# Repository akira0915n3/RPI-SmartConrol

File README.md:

# RPI-SmartConrol
RaspberryPi Zero 用赤外線読み取り、赤外線信号の発信シールドです。<br>
SMD部品を使用しているため、制作難易度は高めです。<br>
部品は秋月電子ですべて揃うはずです。

- Pin配置

|PIN No.|Sources|
|-------|-------|
|Pin 1  |3.3V   |
|Pin 2  |5V     |
|Pin 6  |GND    |
|GPIO 17|LED    |
|GPIO 18|LEDRead|
|Pin 17 |3.3V   |
|Pin 30 |GND    |
|GPIO 12|CN1    |

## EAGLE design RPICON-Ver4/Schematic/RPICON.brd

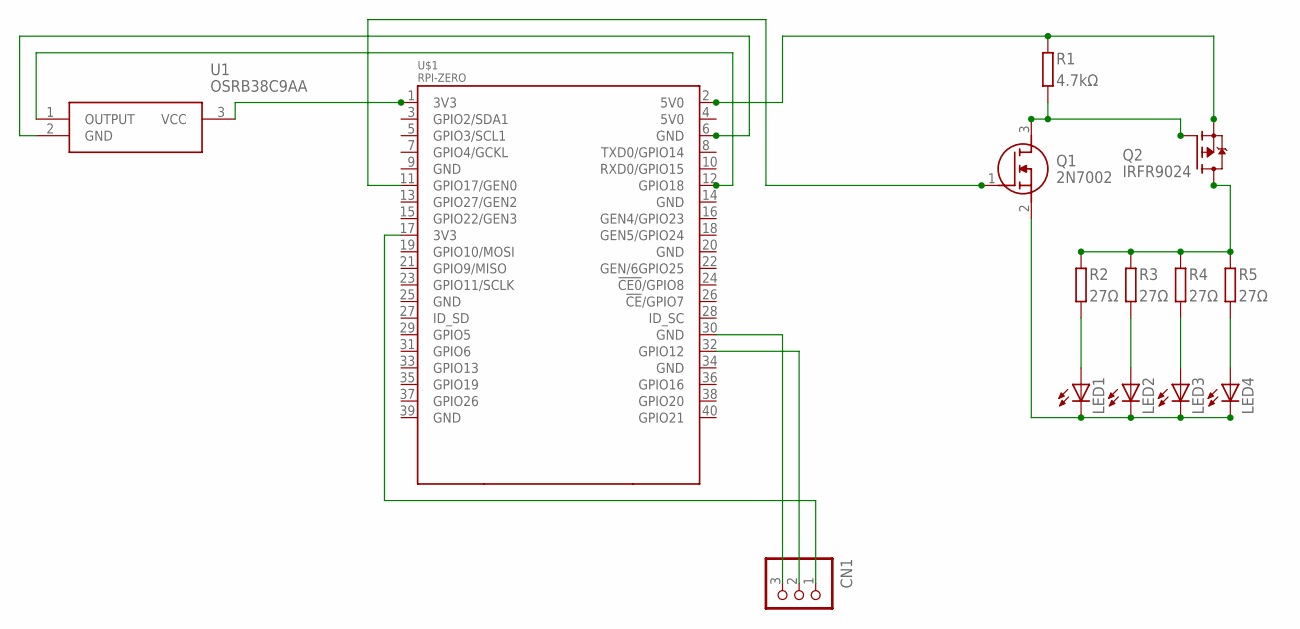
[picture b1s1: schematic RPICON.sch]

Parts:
CN1: S3B-XH-A
LED1, LED2, LED3, LED4: LED5MM
Q1: 2N7002; SOT95P240X120-3N
Q2: IRFR9024; TO252
R1: 4.7kΩ; SMD1608
R2, R3, R4, R5: 27Ω; SMD1608
U1: OSRB38C9AA
U$1: RPI-ZERO; RASPBERRYPI_BASTELSTUBE_V13_RASPI_BOARD_B+_FULL

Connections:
3V3: U1.3 (VCC), U$1.1 (3V3)
3V3@1: CN1.1, U$1.17 (3V3)
5V: Q2.2 (S), R1.1, U$1.2 (5V0)
BGND: LED1.K (C), LED2.K (C), LED3.K (C), LED4.K (C), Q1.2 (S)
GND: U1.2 (GND), U$1.6 (GND)
GND@1: CN1.3, U$1.30 (GND)
unnamed: U1.1 (OUTPUT), U$1.12 (GPIO18)
unnamed: Q1.1 (G), U$1.11 (GPIO17/GEN0)
unnamed: Q1.3 (D), Q2.1 (G), R1.2
unnamed: CN1.2, U$1.32 (GPIO12)
unnamed: Q2.3 (D), R2.1, R3.1, R4.1, R5.1
unnamed: LED1.A, R2.2
unnamed: LED2.A, R3.2
unnamed: LED3.A, R4.2
unnamed: LED4.A, R5.2

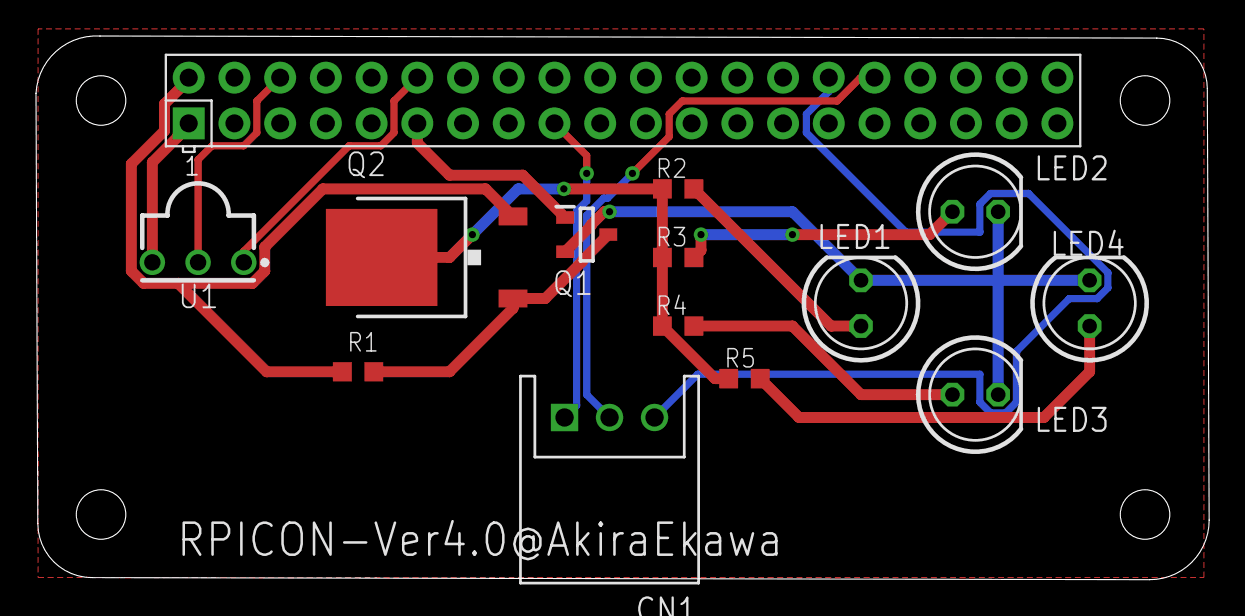
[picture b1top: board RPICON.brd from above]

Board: 2 copper layers, 65.2 x 30.2 mm, 14 parts (0 on the bottom side), 15 nets.
